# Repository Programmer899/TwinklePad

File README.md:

# Twinklepad

This is a small multi task keyboard with 3 custom modes, featuring a TRRS port for double connection, 2 encoders using GPIO and a display for displaying different contents.

Note that the parts that is not a part of the HackPad (https://blueprint.hackclub.com/home) guide will be bought or funded yourself.

---

## Features
1 pcs of 3 step toggle for switching mode
4x4 matrix of key switches
2 pcs of encoders for example slider values such as volume
1 ssd1306 128x32 display for displaying different types of content
1 TRRS port for dual connected modules (could be used for a split keyboard as an example)

---

## Modes

The Twinklepad has 3 modes by default
- Music mode (to the left) - when you press a key it plays a note
- Normal mode (in the middle) - when you press a key it forwards that to the pc as a keycode input
- Calc mode (on the right) - For future calculator mode, able to calculate differents formulas

The current mode for my trinklepad is shown on the display by default.
---

My firmware is written in c from the ground up and has some different features such as:
- Matrix scanning for key inputs
- Encoder control (default: only left is connected to "pitch")
- Display - only capable of displaying mode by default

---

## Hardware

- Raspberry Pi Pico 2 W
- 4x4 MX-style switches  
- 2 pcs Rotary encoders (with push buttons)
- SK6812-MINI-E LEDs 
- SSD1306 128x32 OLED
- Piezo buzzer 4.5 khz
- 3-position mode switch (ON-OFF-ON)

---

## Preview

---

## Getting Started

Clean software:
1. Build with Pico SDK (CMake + Ninja)
2. Flash the `.uf2` file to the Pico
3. Connect via USB and start using HackPad

Use mine?
Just flash the .uf2 file in the fully assembled/production folder.

---

## Notes

This is one of my first times doing something like this.

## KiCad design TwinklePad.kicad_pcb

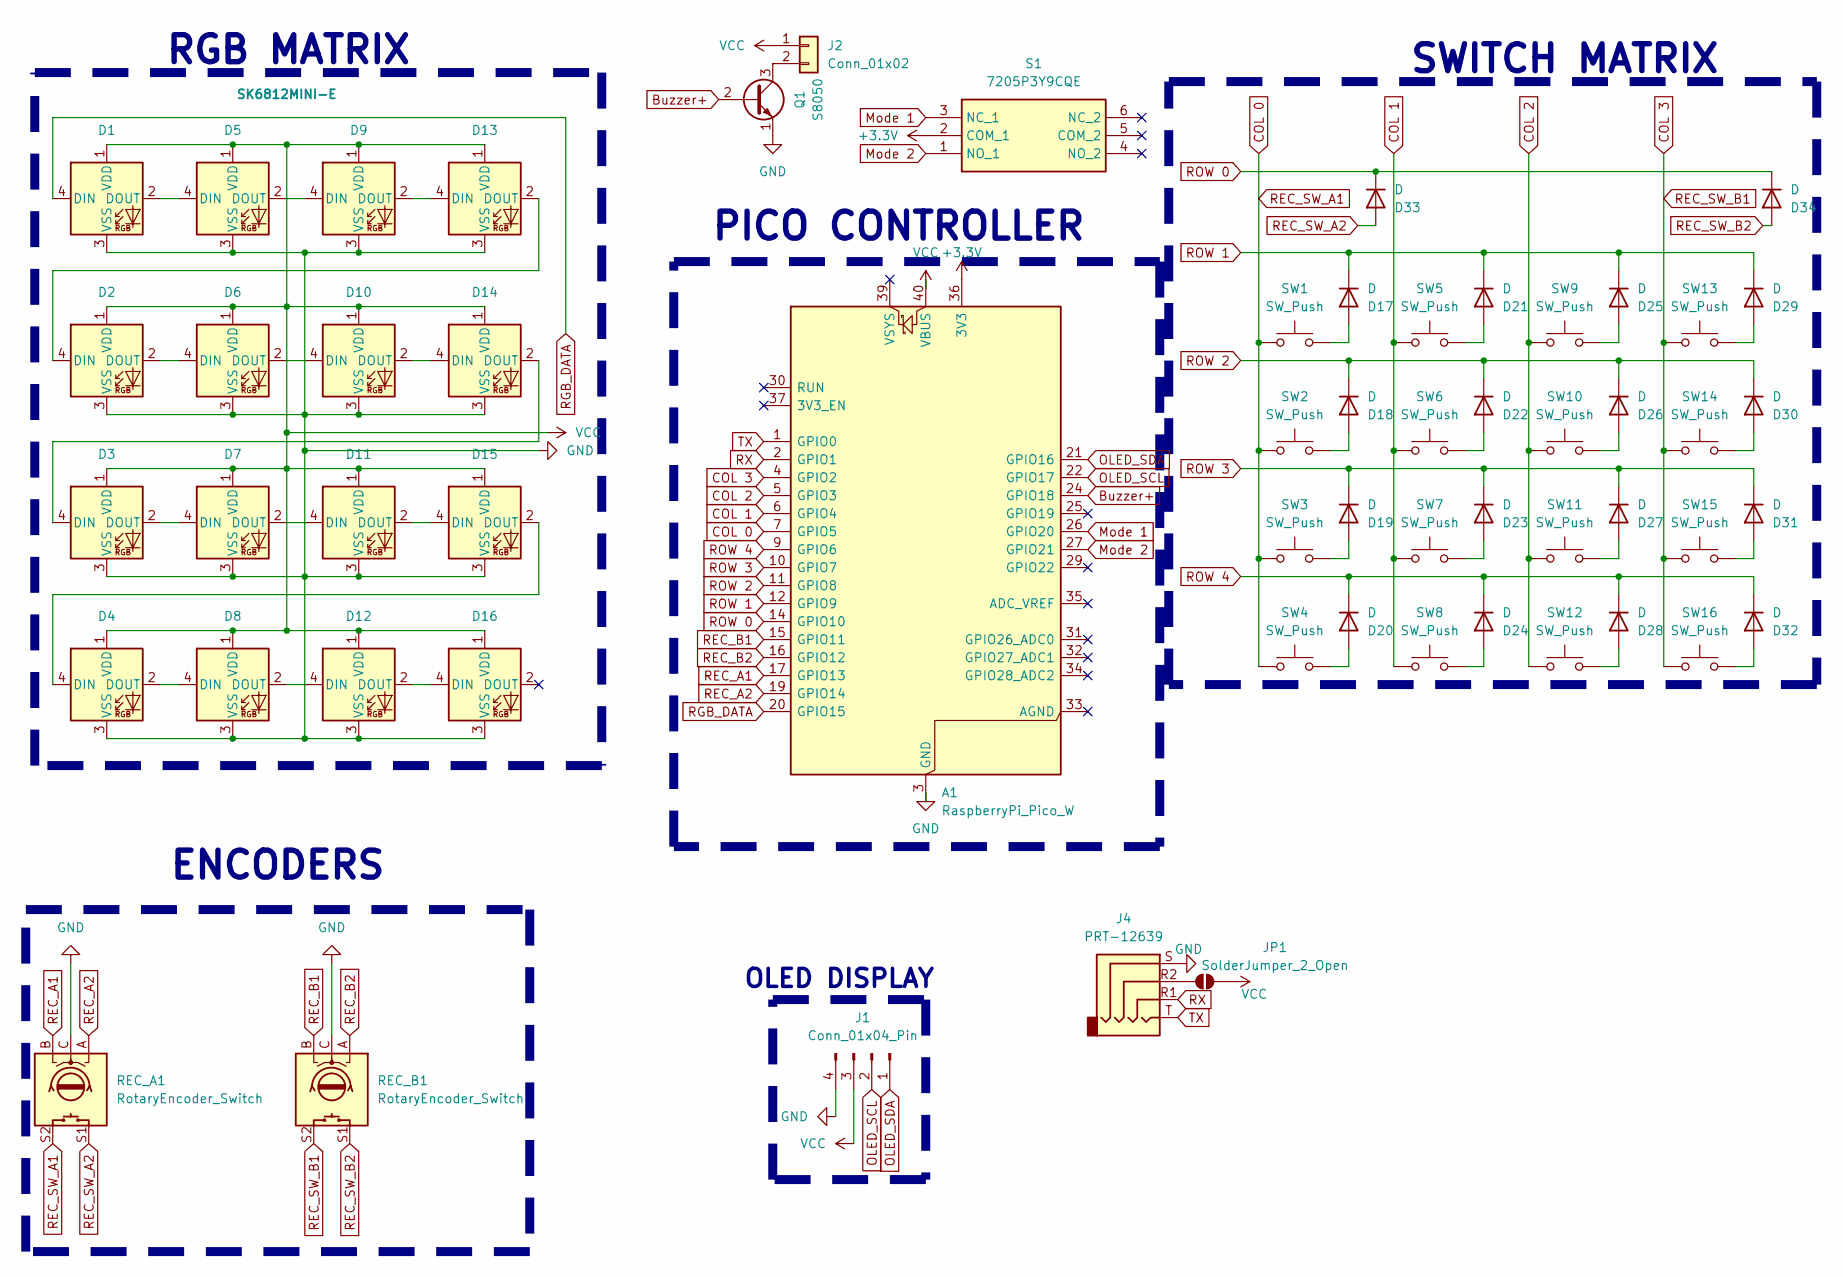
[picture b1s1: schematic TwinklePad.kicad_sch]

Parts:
A1: RaspberryPi_Pico_W; RaspberryPi_Pico_Common_Unspecified
D1, D2, D3, D4, D5, D6, D7, D8, D9, D10, D11, D12, D13, D14, D15, D16: SK6812MINI-E; SK6812MINI-E_fixed
D17, D18, D19, D20, D21, D22, D23, D24, D25, D26, D27, D28, D29, D30, D31, D32, D33, D34: D; D_DO-35_SOD27_P7.62mm_Horizontal
J1: Conn_01x04_Pin; SSD1306-0.91-OLED-4pin-128x32
J2: Conn_01x02; PinHeader_1x02_P2.54mm_Vertical
J4: PRT-12639; PRT12639; Manufacturer_Part_Number PRT-12639; Mouser Part Number 474-PRT-12639
JP1: SolderJumper_2_Open; SolderJumper-2_P1.3mm_Open_RoundedPad1.0x1.5mm
Q1: S8050; TO-92_Inline
REC_A1: RotaryEncoder_Switch; RotaryEncoder_Alps_EC11E-Switch_Vertical_H20mm
REC_B1: RotaryEncoder_Switch; RotaryEncoder_Alps_EC11E-Switch_Vertical_H20mm
S1: 7205P3Y9CQE; Manufacturer_Part_Number 7205P3Y9CQE; Mouser Part Number 611-7205P3Y9CQE
SW1, SW2, SW3, SW4, SW5, SW6, SW7, SW8, SW9, SW10, SW11, SW12, SW13, SW14, SW15, SW16: SW_Push; MX-Hotswap-1U

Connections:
+3.3V: A1.36 (3V3), S1.2 (COM_1)
Buzzer+: A1.24 (GPIO18), Q1.2 (B)
COL 0: A1.7 (GPIO5), REC_A1.S2, SW1.1, SW2.1, SW3.1, SW4.1
COL 1: A1.6 (GPIO4), SW5.1, SW6.1, SW7.1, SW8.1
COL 2: A1.5 (GPIO3), SW9.1, SW10.1, SW11.1, SW12.1
COL 3: A1.4 (GPIO2), REC_B1.S2, SW13.1, SW14.1, SW15.1, SW16.1
GND: A1.3 (GND), A1.8 (GND), A1.13 (GND), A1.18 (GND), A1.23 (GND), A1.28 (GND), A1.38 (GND), D1.3 (VSS), D2.3 (VSS), D3.3 (VSS), D4.3 (VSS), D5.3 (VSS), D6.3 (VSS), D7.3 (VSS), D8.3 (VSS), D9.3 (VSS), D10.3 (VSS), D11.3 (VSS), D12.3 (VSS), D13.3 (VSS), D14.3 (VSS), D15.3 (VSS), D16.3 (VSS), J1.4, J4.S, Q1.1 (E), REC_A1.C, REC_B1.C
Mode 1: A1.26 (GPIO20), S1.3 (NC_1)
Mode 2: A1.27 (GPIO21), S1.1 (NO_1)
unnamed: D1.2 (DOUT), D5.4 (DIN)
unnamed: D2.2 (DOUT), D6.4 (DIN)
unnamed: D3.2 (DOUT), D7.4 (DIN)
unnamed: D4.2 (DOUT), D8.4 (DIN)
unnamed: D5.2 (DOUT), D9.4 (DIN)
unnamed: D6.2 (DOUT), D10.4 (DIN)
unnamed: D10.2 (DOUT), D14.4 (DIN)
unnamed: D7.2 (DOUT), D11.4 (DIN)
unnamed: D11.2 (DOUT), D15.4 (DIN)
unnamed: D8.2 (DOUT), D12.4 (DIN)
unnamed: D12.2 (DOUT), D16.4 (DIN)
unnamed: D9.2 (DOUT), D13.4 (DIN)
unnamed: D2.4 (DIN), D13.2 (DOUT)
unnamed: D3.4 (DIN), D14.2 (DOUT)
unnamed: D4.4 (DIN), D15.2 (DOUT)
unnamed: D17.2 (A), SW1.2
unnamed: D18.2 (A), SW2.2
unnamed: D19.2 (A), SW3.2
unnamed: D20.2 (A), SW4.2
unnamed: D21.2 (A), SW5.2
unnamed: D22.2 (A), SW6.2
unnamed: D23.2 (A), SW7.2
unnamed: D24.2 (A), SW8.2
unnamed: D25.2 (A), SW9.2
unnamed: D26.2 (A), SW10.2
unnamed: D27.2 (A), SW11.2
unnamed: D28.2 (A), SW12.2
unnamed: D29.2 (A), SW13.2
unnamed: D30.2 (A), SW14.2
unnamed: D31.2 (A), SW15.2
unnamed: D32.2 (A), SW16.2
unnamed: J4.R2, JP1.1 (A)
unnamed 41: J2.2, Q1.3 (C); also elsewhere on the board
OLED_SCL: A1.22 (GPIO17), J1.2
OLED_SDA: A1.21 (GPIO16), J1.1
REC_A1: A1.17 (GPIO13), REC_A1.B
REC_A2: A1.19 (GPIO14), REC_A1.A
REC_B1: A1.15 (GPIO11), REC_B1.B
REC_B2: A1.16 (GPIO12), REC_B1.A
REC_SW_A2: D33.2 (A), REC_A1.S1
REC_SW_B2: D34.2 (A), REC_B1.S1
RGB_DATA: A1.20 (GPIO15), D1.4 (DIN)
ROW 0: A1.14 (GPIO10), D33.1 (K), D34.1 (K)
ROW 1: A1.12 (GPIO9), D17.1 (K), D21.1 (K), D25.1 (K), D29.1 (K)
ROW 2: A1.11 (GPIO8), D18.1 (K), D22.1 (K), D26.1 (K), D30.1 (K)
ROW 3: A1.10 (GPIO7), D19.1 (K), D23.1 (K), D27.1 (K), D31.1 (K)
ROW 4: A1.9 (GPIO6), D20.1 (K), D24.1 (K), D28.1 (K), D32.1 (K)
RX: A1.2 (GPIO1), J4.R1
TX: A1.1 (GPIO0), J4.T
VCC: A1.40 (VBUS), D1.1 (VDD), D2.1 (VDD), D3.1 (VDD), D4.1 (VDD), D5.1 (VDD), D6.1 (VDD), D7.1 (VDD), D8.1 (VDD), D9.1 (VDD), D10.1 (VDD), D11.1 (VDD), D12.1 (VDD), D13.1 (VDD), D14.1 (VDD), D15.1 (VDD), D16.1 (VDD), J1.3, J2.1, JP1.2 (B); also elsewhere on the board

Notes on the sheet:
RGB MATRIX
SWITCH MATRIX
PICO CONTROLLER
ENCODERS
OLED DISPLAY

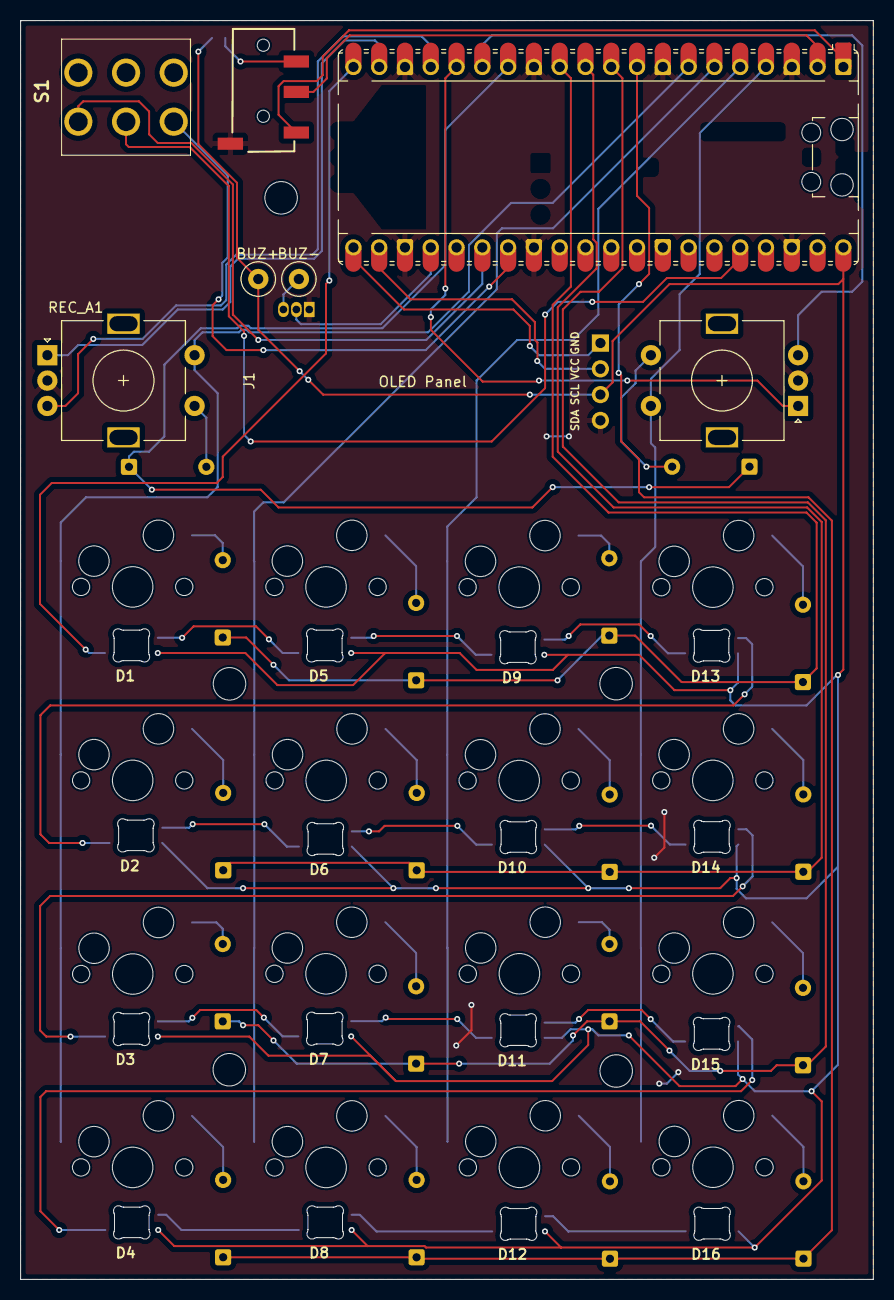
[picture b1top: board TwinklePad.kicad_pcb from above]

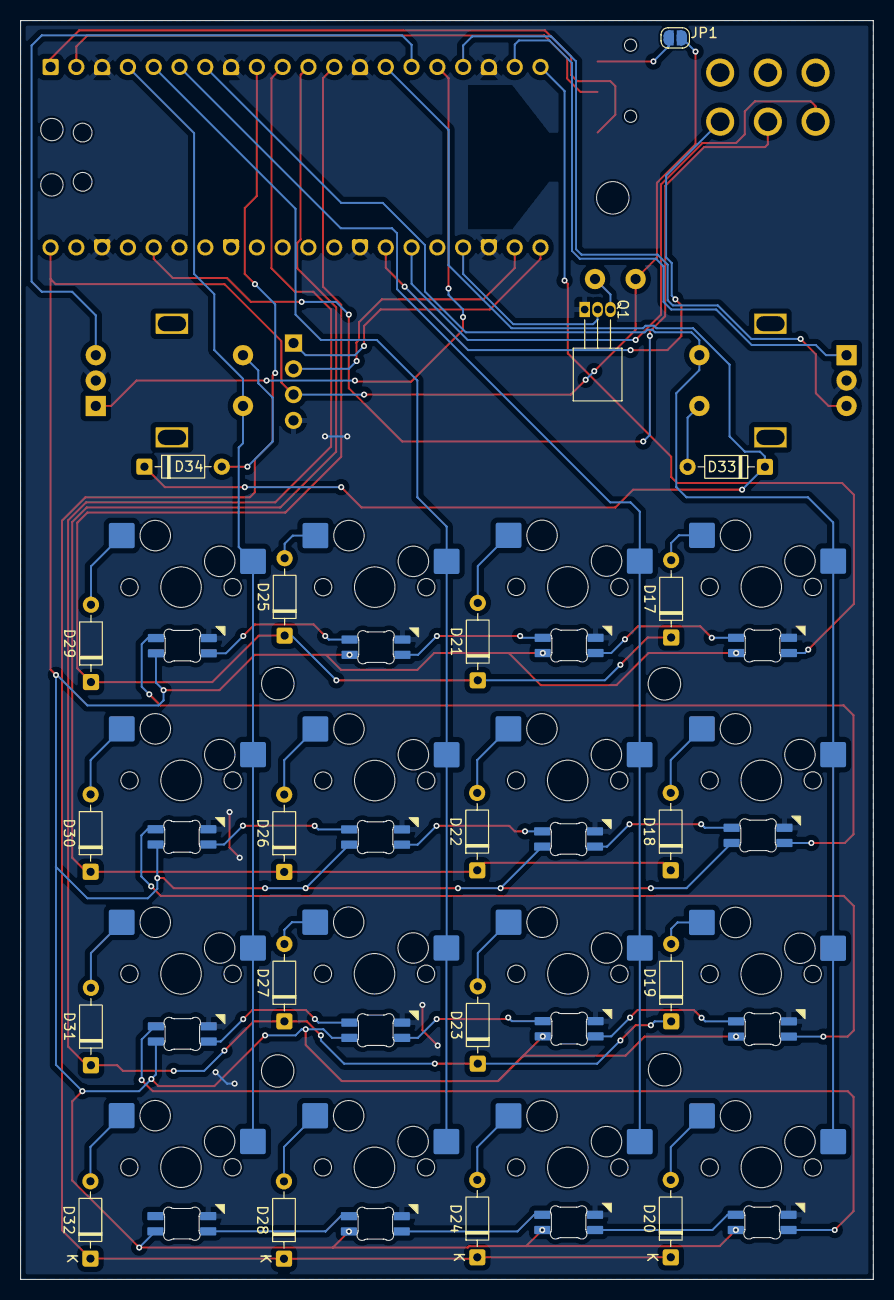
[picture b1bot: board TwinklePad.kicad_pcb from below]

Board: 2 copper layers, 84.0 x 124.0 mm, 60 parts (36 on the bottom side), 59 nets.

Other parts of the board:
BUZ+: TestPoint; TestPoint_Plated_Hole_D2.0mm
BUZ-: TestPoint; TestPoint_Plated_Hole_D2.0mm

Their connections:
unnamed 41: BUZ-.1; also elsewhere on the board
VCC: BUZ+.1; also elsewhere on the board

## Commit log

2026-02-18 Init commit
2026-02-18 Made a complete schematic (maybe)
2026-03-04 Currently moving keys to layout
2026-03-07 Finished current version of the Twinklepad
2026-03-18 Finished PCB
2026-03-21 Updated PCB with new models and schematics
2026-03-25 Finished pcb, schematic and positioning - more or less
2026-03-28 Did some minor changes
2026-03-30 Added a readme for the project
2026-03-30 Ready for production if wanted
2026-03-30 Added readme image
2026-04-03 Updated readme file
2026-04-06 Update README.md #2
2026-04-06 Update README.md #3
